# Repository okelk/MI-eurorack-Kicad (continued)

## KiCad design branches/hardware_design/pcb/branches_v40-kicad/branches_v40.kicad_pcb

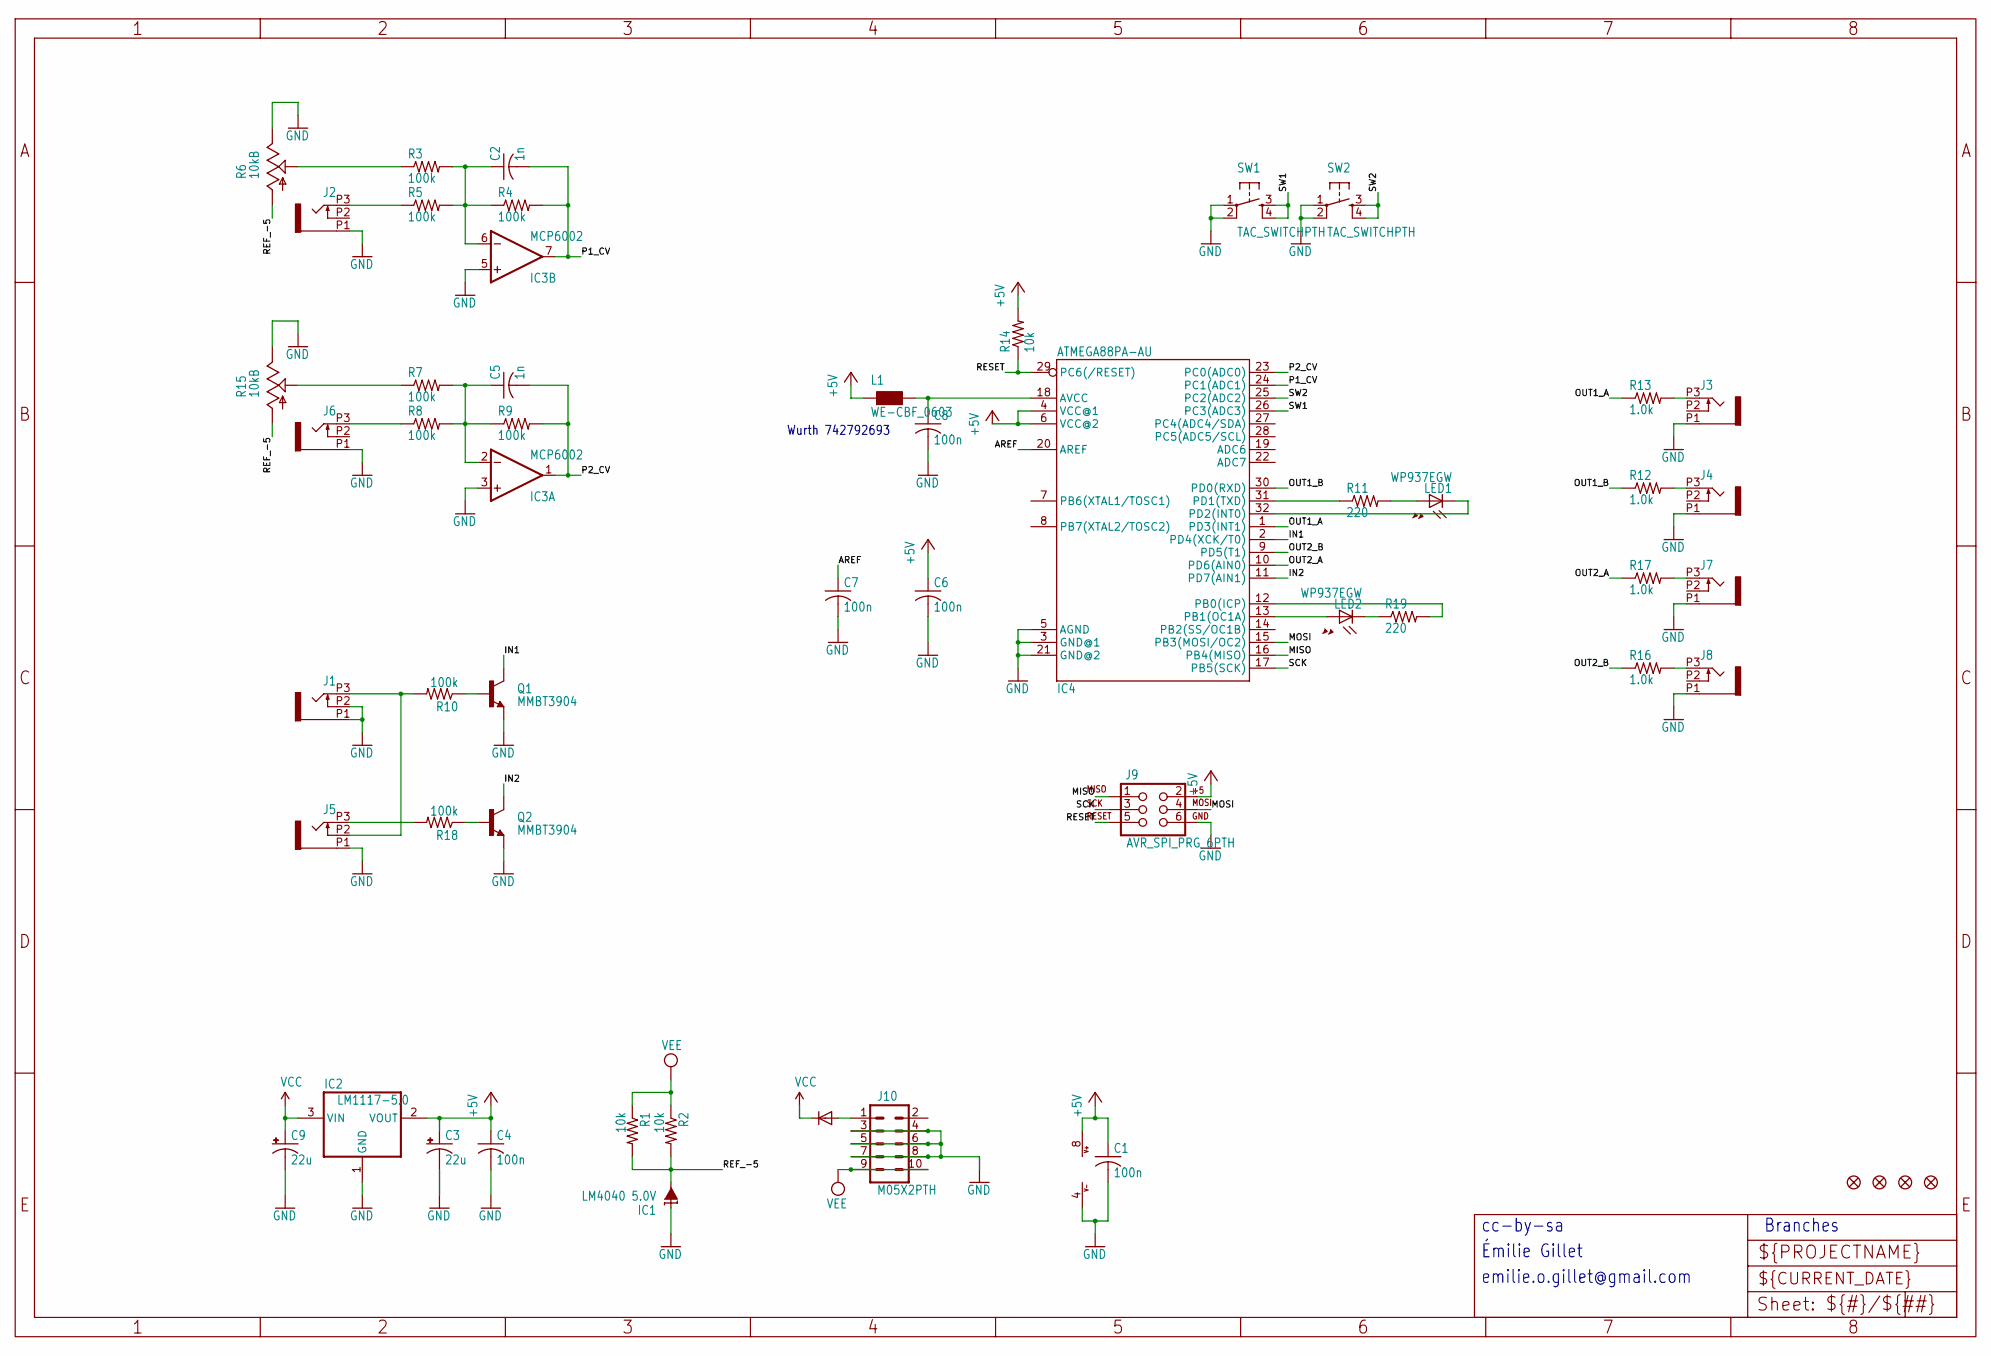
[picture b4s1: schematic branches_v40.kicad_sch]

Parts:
C1, C4, C6, C7, C8: 100n; C0603
C2, C5: 1n; C0603
C3, C9: 22u; PANASONIC_C
D1: 1N5819HW; SOD123
F1, F2, F3, F4: FIDUCIAL1X2; FIDUCIAL-1X2
IC1: LM4040 5.0V; DBZ_R-PDSO-G3
IC2: LM1117-5.0; SOT223
IC3: MCP6002; SO08
IC4: ATMEGA88PA-AU; TQFP32-08
J1, J2, J3, J4, J5, J6, J7, J8: PJ301_THONKICONN6; WQP_PJ_301M6
J9: AVR_SPI_PRG_6PTH; 2X3
J10: M05X2PTH; AVR_ICSP
L1: WE-CBF_0603; 0603
LED1, LED2: WP937EGW; LED3MM
Q1, Q2: MMBT3904; SOT23-BEC
R1, R2, R14: 10k; R0603
R3, R4, R5, R7, R8, R9, R10, R18: 100k; R0603
R6, R15: 10kB; ALPS_POT_VERTICAL_PS
R11, R19: 220; R0603
R12, R13, R16, R17: 1.0k; R0603
SW1, SW2: TAC_SWITCHPTH; TACTILE-PTH

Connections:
+5V: C1.1, C3.+, C4.1, C6.1, IC2.2 (VOUT), IC3.8 (V+), IC4.4 (VCC@1), IC4.6 (VCC@2), J9.2, L1.1, R14.2
AREF: C7.1, IC4.20 (AREF)
GATE1_IN: J1.P3 (3), J5.P2 (2), R10.2
GATE2_IN: J5.P3 (3), R18.2
GND: C1.2, C3.-, C4.2, C6.2, C7.2, C8.2, C9.-, IC1.1 (C), IC2.1 (GND), IC3.3 (+IN), IC3.4 (V-), IC3.5 (+IN), IC4.3 (GND@1), IC4.5 (AGND), IC4.21 (GND@2), J1.P1 (1), J1.P2 (2), J2.P1 (1), J3.P1 (1), J4.P1 (1), J5.P1 (1), J6.P1 (1), J7.P1 (1), J8.P1 (1), J9.6, J10.3, J10.4, J10.5, J10.6, J10.7, J10.8, Q1.E, Q2.E, R6.P$1 (E), R15.P$1 (E), SW1.1, SW1.2, SW2.1, SW2.2
IN1: IC4.2 (PD4(XCK/T0)), Q1.C
IN2: IC4.11 (PD7(AIN1)), Q2.C
MISO: IC4.16 (PB4(MISO)), J9.1
MOSI: IC4.15 (PB3(MOSI/OC2)), J9.4
unnamed: Q1.B, R10.1
unnamed: Q2.B, R18.1
unnamed: D1.A, J10.1
unnamed: C5.1, IC3.2 (-IN), R7.2, R8.2, R9.1
unnamed: J8.P3 (3), R16.2
unnamed: R7.1, R15.P$2 (S)
unnamed: R3.1, R6.P$2 (S)
unnamed: J2.P3 (3), R5.1
unnamed: J6.P3 (3), R8.1
unnamed: IC4.31 (PD1(TXD)), R11.1
unnamed: LED1.A, R11.2
unnamed: IC4.32 (PD2(INT0)), LED1.K (C)
unnamed: IC4.13 (PB1(OC1A)), LED2.A
unnamed: LED2.K (C), R19.1
unnamed: IC4.12 (PB0(ICP)), R19.2
unnamed: C2.1, IC3.6 (-IN), R3.2, R4.1, R5.2
unnamed: J3.P3 (3), R13.2
unnamed: J4.P3 (3), R12.2
unnamed: J7.P3 (3), R17.2
unnamed: C8.1, IC4.18 (AVCC), L1.2
OUT1_A: IC4.1 (PD3(INT1)), R13.1
OUT1_B: IC4.30 (PD0(RXD)), R12.1
OUT2_A: IC4.10 (PD6(AIN0)), R17.1
OUT2_B: IC4.9 (PD5(T1)), R16.1
P1_CV: C2.2, IC3.7 (OUT), IC4.24 (PC1(ADC1)), R4.2
P2_CV: C5.2, IC3.1 (OUT), IC4.23 (PC0(ADC0)), R9.2
REF_-5: IC1.2 (A), R1.2, R2.2, R6.P$3 (A), R15.P$3 (A)
RESET: IC4.29 (PC6(/RESET)), J9.5, R14.1
SCK: IC4.17 (PB5(SCK)), J9.3
SW1: IC4.26 (PC3(ADC3)), SW1.3, SW1.4
SW2: IC4.25 (PC2(ADC2)), SW2.3, SW2.4
VCC: C9.+, D1.C, IC2.3 (VIN)
VEE: J10.9, J10.10, R1.1, R2.1

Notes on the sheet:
cc-by-sa
Branches
emilie.o.gillet@gmail.com
Wurth 742792693
Émilie Gillet

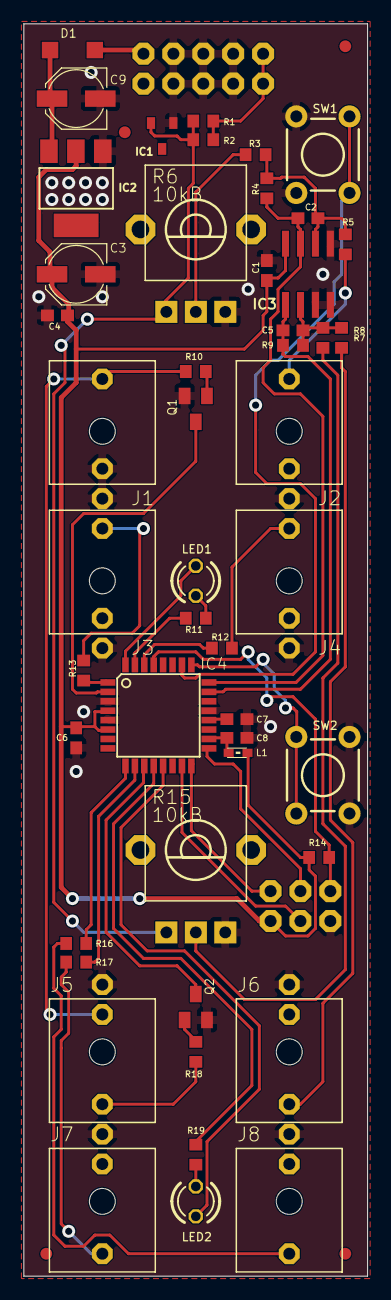
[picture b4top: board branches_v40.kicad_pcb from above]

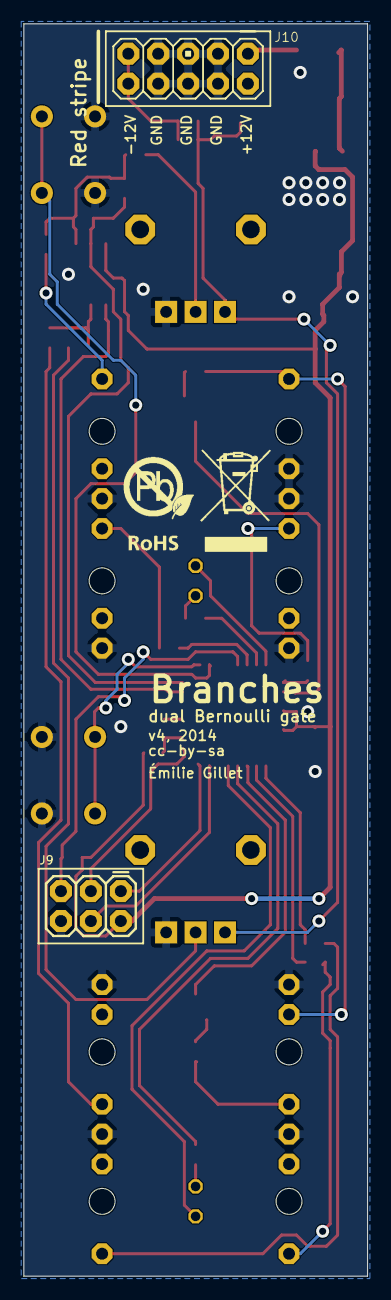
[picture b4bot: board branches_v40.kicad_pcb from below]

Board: 2 copper layers, 29.2 x 106.4 mm, 55 parts (3 on the bottom side), 42 nets.

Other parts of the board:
U$1: ROHS

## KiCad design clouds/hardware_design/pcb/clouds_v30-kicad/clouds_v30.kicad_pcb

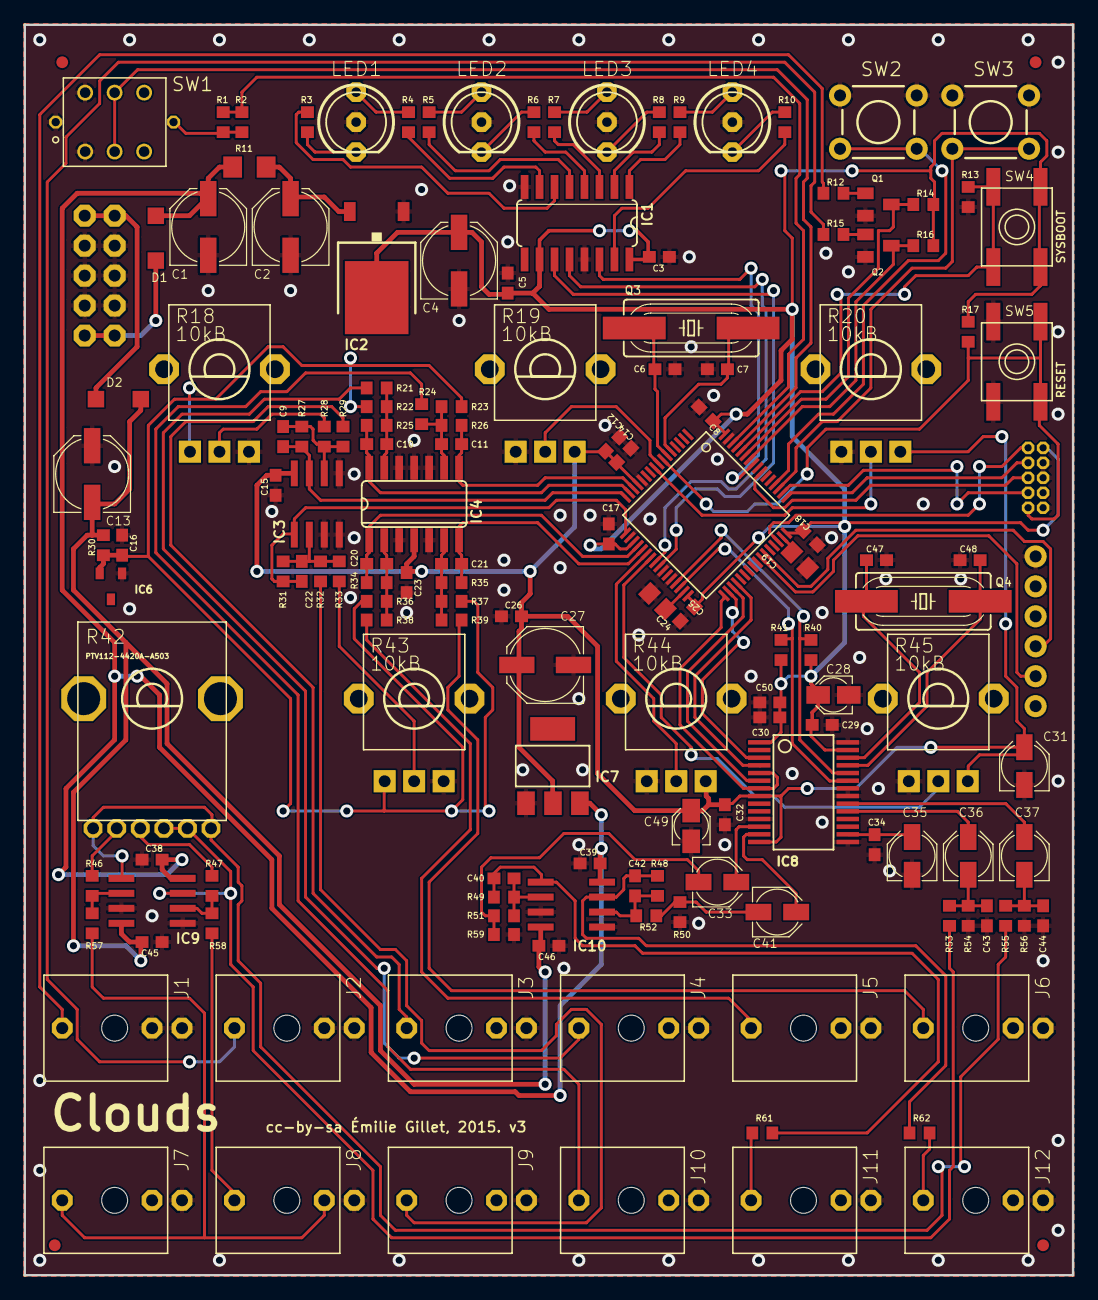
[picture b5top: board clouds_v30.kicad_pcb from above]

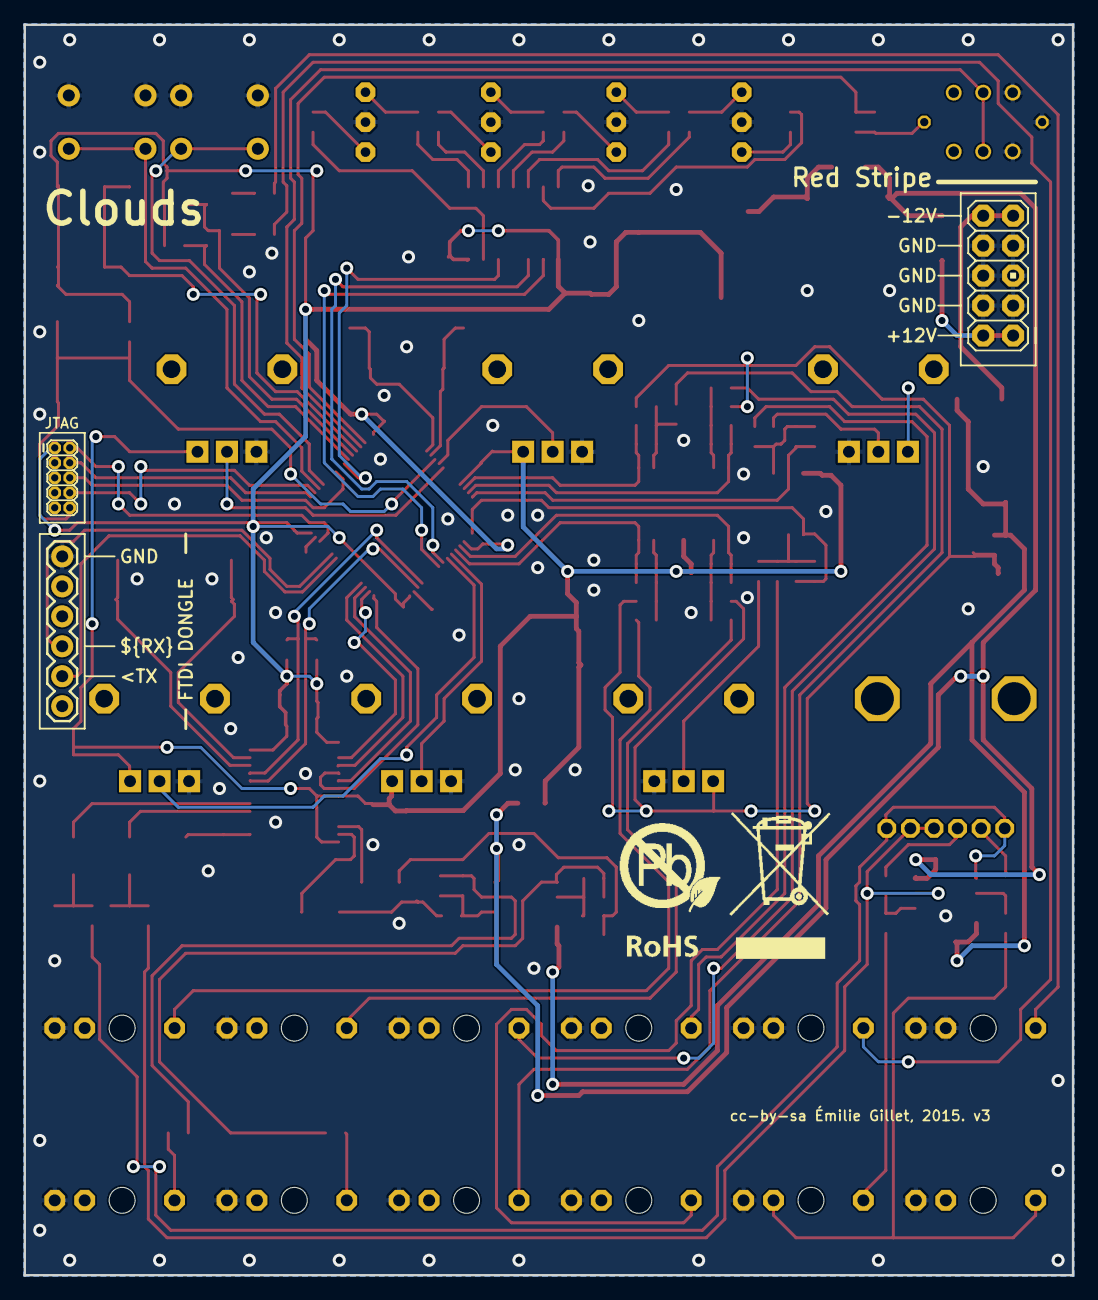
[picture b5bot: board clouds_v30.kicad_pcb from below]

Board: 2 copper layers, 88.9 x 106.0 mm, 156 parts (4 on the bottom side), 106 nets.

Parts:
C1, C2, C4, C13, C27: 47u; PANASONIC_D
C3, C5, C8, C14, C15, C16, C17, C18, C23, C25, C26, C29, C30, C32, C34, C38, C39, C45, C46: 100n; C0603
C6, C7, C40, C42, C47, C48: 18p; C0603
C9, C10, C11, C20, C21, C22: 1n; C0603
C12, C50: 1u; C0603
C19, C24: 2.2u; C0805
C28, C49: 10u; PANASONIC_A
C31, C33, C35, C36, C37, C41: 10u; PANASONIC_B
C43, C44: 220p; C0603
D1, D2: 1N5819HW; SOD123
F1, F2, F3, F4: FIDUCIAL1X2; FIDUCIAL-1X2
IC1: 74HC595D; SO16
IC2: LM1117-3.3; TO252
IC3: MCP6002; SO08
IC4: MCP6004; SO14
IC5: STM32F405RGT6; TQFP-10X10-64
IC6: LM4040B10; DBZ_R-PDSO-G3
IC7: LM1117-3.3; SOT223
IC8: WM8731; SSOP28
IC9, IC10: TL072D; SO08
J1, J2, J3, J4, J5, J6, J7, J8, J9, J10, J11, J12: PJ301_THONKICONN6; WQP_PJ_301M6
JP1: 1X06
JP2: M05X2MINIJTAG; 2X5-1.27
JP3: M05X2PTH; AVR_ICSP
LED1, LED2, LED3, LED4: WP59EGW; LED-BICOLOR-THROUGHHOLE-5MM
Q1, Q2: MMBT3904; SOT23-BEC
Q3: 8MHz; HC49UP
Q4: 12.288MHz; HC49UP
R1, R2, R3, R4, R5, R6, R7, R8, R9, R10: 68; R0603
R11: 4.7; R1206
R12, R15, R21, R24, R29, R32, R38, R39: 100k; R0603
R13, R14, R16, R17: 10k; R0603
R18, R19, R20, R43, R44, R45: 10kB; ALPS_POT_VERTICAL_PS
R22, R23, R28, R33, R37: 200k; R0603
R25, R26, R35: 33k; R0603
R27, R31: 66.5k; R0603
R30: 470; R0603
R34: 47k; R0603
R36: 180k; R0603
R40, R41: 2.2k; R0603
R42: PTV112-4420A-A503; BOURNS_PTV112
R46, R47: 3.3k; R0603
R48, R49, R50, R59: 39k; R0603
R51, R52, R53, R54, R55, R56: 5.6k; R0603
R57, R58: 22k; R0603
R61, R62: 1.0k; R0603
SW1: LP4OA1PBCT
SW2, SW3: TACTILE-PTH
SW4, SW5: EVQ-Q2
U$2: ROHS_BIG

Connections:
+3V3: C3.1, C4.+, C5.1, C8.1, C17.1, C18.1, C25.1, C28.+, C29.1, C30.1, C50.1, IC1.10, IC1.16, IC2.3, IC5.19, IC5.32, IC5.48, IC5.64, IC8.1, IC8.27, JP2.1, R14.2, R16.2, R17.2, R40.2, R41.2, SW4.B, SW4.B'
+3V3_A: C12.1, C14.1, C15.1, C23.1, C26.1, C27.+, C31.+, C32.1, C49.+, IC3.8, IC4.4, IC5.13, IC7.2, IC8.8, IC8.14, R19.P$1, R20.P$1, R44.P$1, R45.P$1
AREF_-10: C16.1, IC6.2, R18.P$3, R22.2, R23.2, R30.2, R36.2, R37.2, R43.P$3
BLEND_CV: C21.2, IC4.7, IC5.21, R35.1
BLEND_POT: IC5.23, R45.P$2
BOOT_FLASH: IC5.60, R13.2, SW4.A, SW4.A'
DENSITY_CV: C22.2, IC3.1, IC5.17, R31.1
GND: C1.-, C2.-, C3.2, C4.-, C5.2, C6.1, C7.1, C8.2, C12.2, C13.+, C14.2, C15.2, C16.2, C17.2, C18.2, C19.2, C23.2, C24.2, C25.2, C26.2, C27.-, C28.-, C29.2, C30.2, C31.-, C32.2, C34.2, C35.-, C38.2, C39.2, C43.2, C44.2, C45.1, C46.1, C47.1, C48.1, C49.-, C50.2, IC1.8, IC1.13, IC2.1, IC3.3, IC3.4, IC3.5, IC4.3, IC4.5, IC4.10, IC4.11, IC4.12, IC5.12, IC5.18, IC5.26, IC5.28, IC5.63, IC6.1, IC7.1, IC8.11, IC8.15, IC8.21, IC8.22, IC8.28, IC9.3, IC9.5, IC10.3, IC10.5, J1.P1, J1.P2, J2.P1, J2.P2, J3.P1, J4.P1, J5.P1, J6.P1, J7.P1, J8.P1, J9.P1, J10.P1, J11.P1, J12.P1, JP1.1, JP2.3, JP2.5, JP2.9, JP3.3, JP3.4, JP3.5, JP3.6, JP3.7, JP3.8, LED1.2, LED2.2, LED3.2, LED4.2, Q1.E, Q2.E, R13.1, R18.P$1, R19.P$3, R20.P$3, R43.P$1, R44.P$3, R45.P$3, R50.1, R54.1, R56.1, R59.1, SW1.L2, SW1.P3, SW1.P6, SW2.1, SW2.2, SW3.1, SW3.2, SW5.A, SW5.A'
I2C_SCL: IC5.29, IC8.24, R40.1
I2C_SDA: IC5.30, IC8.23, R41.1
I2S_LRCK: IC5.33, IC8.5, IC8.7
I2S_SCK: IC5.34, IC8.3
I2S_SIN: IC5.35, IC8.6
I2S_SOUT: IC5.36, IC8.4
JTCK: IC5.49, JP2.4
JTDI: IC5.50, JP2.8
JTDO: IC5.55, JP2.6
JTMS: IC5.46, JP2.2
LED_DATA: IC1.14, IC5.57
LED_EN: IC1.12, IC5.24
LED_REC: IC5.62, R1.1, R2.1
LED_SCK: IC1.11, IC5.25
LIN: C37.+, IC8.20
LOUT: C33.+, IC8.12
LOUT_JACK: J11.P3, R61.1
unnamed: J4.P3, R21.2
unnamed: C10.1, IC4.13, R21.1, R22.1, R25.2
unnamed: J10.P3, R24.2
unnamed: C11.1, IC4.9, R23.1, R24.1, R26.2
unnamed: J6.P3, R39.2
unnamed: C7.2, IC5.5, Q3.2
unnamed: C6.2, IC5.6, Q3.1
unnamed: LED4.3, R9.1
unnamed: J5.P3, R38.2
unnamed: C20.1, IC4.2, R34.2, R36.1, R38.1
unnamed: LED4.1, R10.1
unnamed: C19.1, IC5.47
unnamed: J9.P3, R32.2
unnamed: C21.1, IC4.6, R35.2, R37.1, R39.1
unnamed: LED3.1, R8.1
unnamed: C34.1, C35.+, IC8.16
unnamed: C37.-, C44.1, R55.1, R56.2
unnamed: C24.1, IC5.31
unnamed: J8.P3, R58.2
unnamed: J7.P3, J8.P2, R57.2
unnamed: C36.-, C43.1, R53.1, R54.2
unnamed: C41.-, R50.2, R52.2
unnamed: C22.1, IC3.2, R31.2, R32.1, R33.1
unnamed: C42.1, IC10.6, R48.2, R52.1
unnamed: R33.2, R43.P$2
unnamed: J3.P3, R29.2
unnamed: C42.2, IC10.7, R48.1, R62.2
unnamed: LED3.3, R7.1
unnamed: C9.1, IC3.6, R27.2, R28.1, R29.1
unnamed: C33.-, R51.2, R59.2
unnamed: C40.1, IC10.2, R49.2, R51.1
unnamed: C40.2, IC10.1, R49.1, R61.2
unnamed: LED2.1, R6.1
unnamed: R18.P$2, R28.2
unnamed: J2.P3, R15.1
unnamed: Q2.B, R15.2
unnamed: R1.2, R2.2, SW1.L1
unnamed: LED2.3, R5.1
unnamed: LED1.1, R3.1
unnamed: LED1.3, R4.1
unnamed: IC9.7, R42.2P, R42.3P, R53.2
unnamed: IC1.15, R10.2
unnamed: IC1.1, R9.2
unnamed: IC1.2, R8.2
unnamed: IC1.3, R7.2
unnamed: IC1.4, R6.2
unnamed: IC1.5, R5.2
unnamed: IC1.6, R3.2
unnamed: IC1.7, R4.2
unnamed: IC9.1, R42.2, R42.3, R55.2
unnamed: R42.1P, R47.1
unnamed: R42.1, R46.1
unnamed: IC9.6, R47.2, R58.1
unnamed: C2.+, IC2.2, R11.2
unnamed: D1.A, JP3.1, JP3.2
unnamed: J1.P3, R12.1
unnamed: IC9.2, R46.2, R57.1
unnamed: C47.2, IC8.26, Q4.1
unnamed: C48.2, IC8.25, Q4.2
unnamed: D2.C, JP3.9, JP3.10
unnamed: Q1.B, R12.2
PITCH_POT: IC5.9, R20.P$2
PLAY: IC5.58, Q2.C, R16.1
POSITION_POT_CV: C9.2, IC3.7, IC5.16, R27.1
REC: IC5.59, Q1.C, R14.1
RESET: IC5.7, JP2.10, R17.1, SW5.B, SW5.B'
RIN: C36.+, IC8.19
ROUT: C41.+, IC8.13
ROUT_JACK: J12.P3, R62.1
RX: IC5.43, JP1.4
SIZE_CV: C10.2, IC4.14, IC5.15, R25.1
SIZE_POT: IC5.8, R19.P$2
SW_LOAD: IC5.51, SW3.3, SW3.4
SW_MODE: IC5.52, SW2.3, SW2.4
SW_REC: IC5.61, SW1.P2, SW1.P5
TEXTURE_CV: C11.2, IC4.8, IC5.14, R26.1
TEXTURE_POT: IC5.22, R44.P$2
TX: IC5.42, JP1.5
VCC: C1.+, C38.1, C39.1, D1.C, IC7.3, IC9.8, IC10.8, R11.1
VEE: C13.-, C45.2, C46.2, D2.A, IC9.4, IC10.4, R30.1
V_OCT: C20.2, IC4.1, IC5.20, R34.1

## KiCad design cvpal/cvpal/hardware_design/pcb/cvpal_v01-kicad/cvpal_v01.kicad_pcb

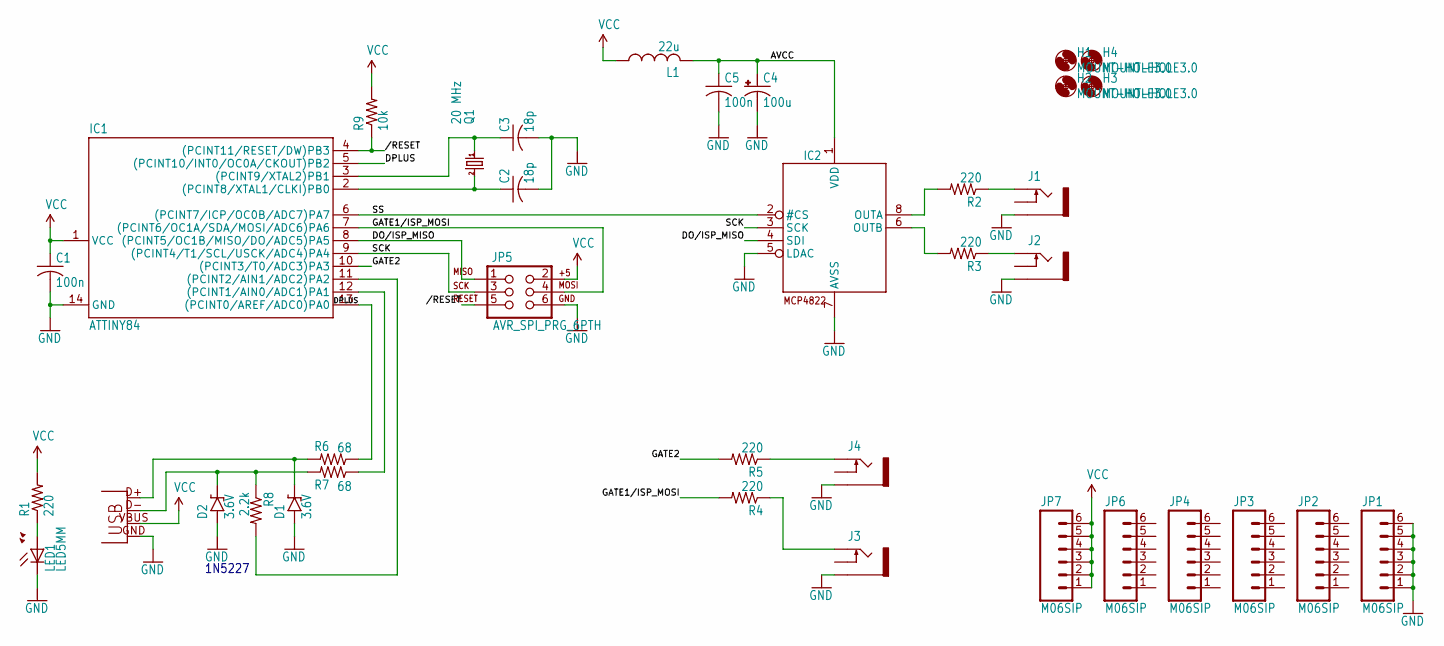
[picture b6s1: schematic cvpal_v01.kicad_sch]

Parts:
C1, C5: 100n; C025-025X050
C2, C3: 18p; C025-025X050
C4: 100u; E2,5-7
D1, D2: 3.6V; D-5
H1, H2, H3, H4: MOUNT-HOLE3.0; 3,0
IC1: ATTINY84; DIL14
IC2: MCP4822; DIL08
J1, J2, J3, J4: 1503_12
JP1, JP2, JP3, JP4, JP6, JP7: M06SIP; 1X06
JP5: AVR_SPI_PRG_6PTH; 2X3
L1: 22u; 0207_10
LED1: LED5MM
Q1: 20 MHz; HC49_S
R1, R2, R3, R4, R5: 220; 0204_7
R6, R7: 68; 0204_7
R8: 2.2k; 0204_7
R9: 10k; 0204_7
X2: USBPTH; USB-B-PTH

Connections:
/RESET: IC1.4 ((PCINT11/RESET/DW)PB3), JP5.5, R9.1
AVCC: C4.+, C5.1, IC2.1 (VDD), L1.2
CV1: IC2.8 (OUTA), R2.2
CV1_R: J1.3 (2), R2.1
CV2: IC2.6 (OUTB), R3.2
D+: D1.C, R6.2, X2.D+
D-: D2.C, R7.2, R8.1, X2.D-
DMINUS: IC1.12 ((PCINT1/AIN0/ADC1)PA1), R7.1
DO/ISP_MISO: IC1.8 ((PCINT5/OC1B/MISO/DO/ADC5)PA5), IC2.4 (SDI), JP5.1
DPLUS: IC1.5 ((PCINT10/INT0/OC0A/CKOUT)PB2), IC1.13 ((PCINT0/AREF/ADC0)PA0), R6.1
GATE1/ISP_MOSI: IC1.7 ((PCINT6/OC1A/SDA/MOSI/ADC6)PA6), JP5.4, R4.2
GATE2: IC1.10 ((PCINT3/T0/ADC3)PA3), R5.2
GND: C1.2, C2.2, C3.2, C4.-, C5.2, D1.A, D2.A, IC1.14 (GND), IC2.5 (LDAC), IC2.7 (AVSS), J1.5 (1), J2.5 (1), J3.5 (1), J4.5 (1), JP1.1, JP1.2, JP1.3, JP1.4, JP1.5, JP1.6, JP5.6, LED1.K (C), X2.GND
unnamed: LED1.A, R1.1
unnamed: C3.1, IC1.3 ((PCINT9/XTAL2)PB1), Q1.1
unnamed: C2.1, IC1.2 ((PCINT8/XTAL1/CLKI)PB0), Q1.2
unnamed: J2.3 (2), R3.1
unnamed: J4.3 (2), R5.1
unnamed: IC1.11 ((PCINT2/AIN1/ADC2)PA2), R8.2
unnamed: J3.3 (2), R4.1
SCK: IC1.9 ((PCINT4/T1/SCL/USCK/ADC4)PA4), IC2.3 (SCK), JP5.3
SS: IC1.6 ((PCINT7/ICP/OC0B/ADC7)PA7), IC2.2 (#CS)
VCC: C1.1, IC1.1 (VCC), JP5.2, JP7.1, JP7.2, JP7.3, JP7.4, JP7.5, JP7.6, L1.1, R1.2, R9.2, X2.VBUS

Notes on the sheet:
1N5227

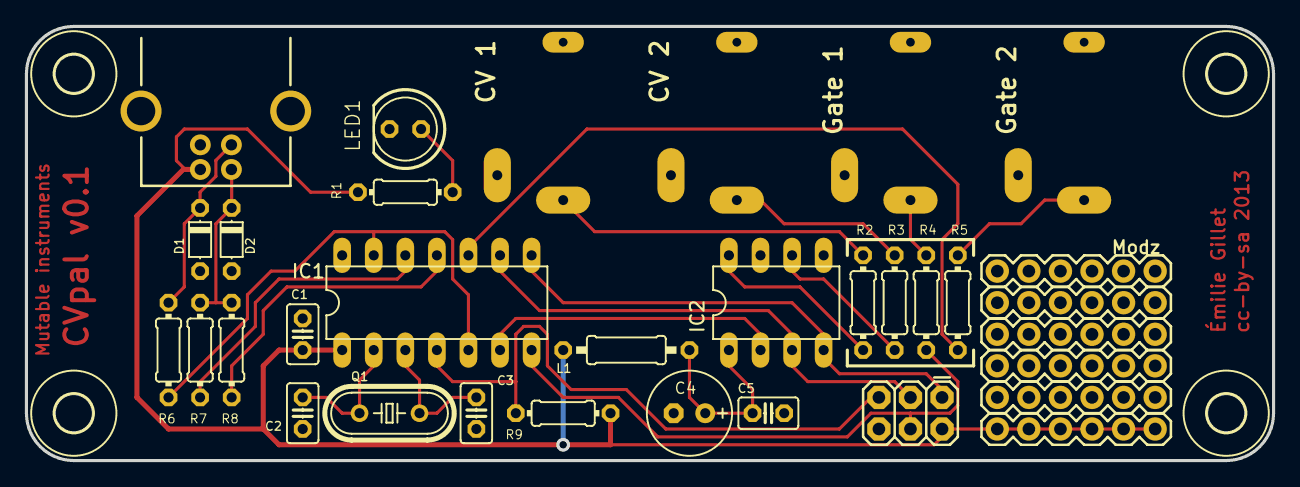
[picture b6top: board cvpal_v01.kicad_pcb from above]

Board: 2 copper layers, 100.3 x 34.9 mm, 37 parts (0 on the bottom side), 23 nets.

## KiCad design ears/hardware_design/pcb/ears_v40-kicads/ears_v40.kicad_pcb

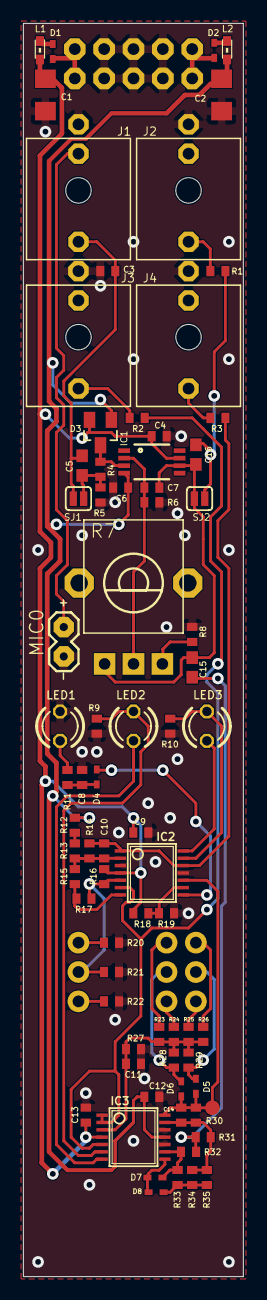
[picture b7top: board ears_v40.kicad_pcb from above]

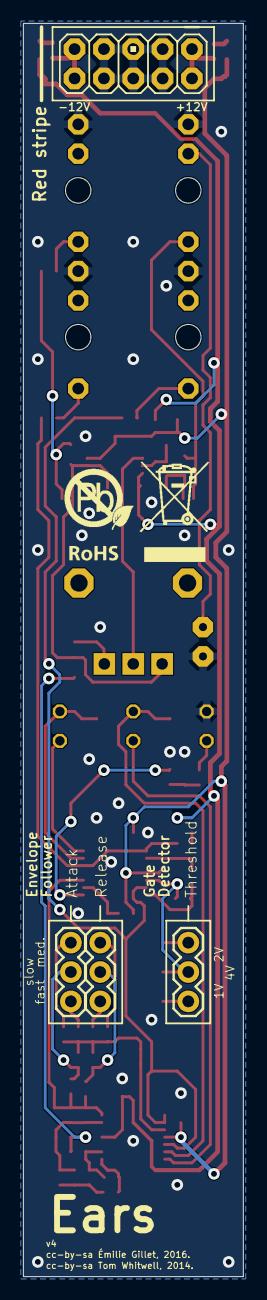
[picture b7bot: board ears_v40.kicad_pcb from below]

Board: 2 copper layers, 19.0 x 108.4 mm, 80 parts (5 on the bottom side), 47 nets.

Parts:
C1, C2: 22u; C1206
C3, C10: 68p; C0402
C4, C6, C9, C12, C13: 100n; C0402
C5, C15, C16: 4.7u; C0603
C7: 22p; C0402
C8, C11: 1u; C0402
C14: 1.0n; C0402
D1, D2: PMEG2010AEB; SOD523
D3: DNP; SOT23
D4, D5, D6, D7, D8: 1N4148; SOD523
IC1: OPA1641; MSOP8
IC2, IC3: LM324PW; TSSOP14
J1, J2, J3, J4: PJ301_THONKICONN6; WQP_PJ_301M6
JP1, JP2, JP3: 1X03
JP4: M05X2PTH; AVR_ICSP
L1, L2: 0603
LED1: WP710A10SEC/J3; LED3MM
LED2: AOL-3MWY4; LED3MM
LED3: WP710A10SEC/J4; LED3MM
MIC0: 1X02_TINY
R1, R2, R3, R8: 510; R0402
R4, R6, R10, R11, R24: 10k; R0402
R5, R27: 1.0M; R0402
R7: 50kB; ALPS_POT_VERTICAL_PS
R9, R18, R22, R26: 20k; R0402
R12, R19, R20, R21, R23, R29, R33, R34, R35: 100k; R0402
R13, R14, R15, R16, R17, R30, R31, R32: 200k; R0402
R25: 2.7k; R0402
R28: 430k; R0402
SJ1, SJ2: SOLDERJUMPERNC; SJ_2S
TP1: TEST-POINT3X5; PAD.03X.05
U$2: ROHS

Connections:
AMP_OUT: C7.2, C15.1, C16.1, IC1.6, R7.P$3, SJ2.1
AMP_OUT_AC: C15.2, R31.1, R32.1
CLIP: D4.A, IC2.8
ENVELOPE: IC2.6, IC3.1, IC3.2, IC3.5, R2.1
FULL_WAVE_RECT: C14.2, D5.A, D6.C, IC2.10, IC3.14, R30.2, TP1.P$1
GATE: C10.2, IC2.1, IC2.12, R3.1, R14.2
GND: C1.2, C2.1, C3.2, C4.2, C6.1, C8.2, C9.2, C11.2, C12.1, C13.2, IC2.3, IC2.11, IC3.10, IC3.12, J1.P1, J2.P1, J3.P1, J4.P1, JP4.3, JP4.4, JP4.5, JP4.6, JP4.7, JP4.8, LED1.K, MIC0.1, R5.1, R6.2, R8.2, R9.2, R10.1, R19.1, R20.2, R21.2, R22.2, R27.1
unnamed: D3.3, IC1.3, R4.1
unnamed: J2.P3, R1.2
unnamed: C3.1, C5.1, J1.P3, SJ1.1
unnamed: D7.A, D8.C, IC3.8
unnamed: D1.A, JP4.1, JP4.2
unnamed: J1.P2, MIC0.2
unnamed: C10.1, IC2.2, R13.2, R14.1, R15.2
unnamed: C7.1, IC1.2, R6.1, R7.P$2
unnamed: C5.2, R4.2, R5.2, SJ1.2
unnamed: D7.C, IC3.9, R32.2, R33.1
unnamed: D8.A, R33.2, R34.1, R35.1
unnamed: R7.P$1, R8.1
unnamed: C14.1, IC3.13, R30.1, R31.2, R34.2, R35.2
unnamed: C16.2, R1.1, SJ2.2
unnamed: J3.P3, R2.2
unnamed: IC3.6, LED2.K, R9.1
unnamed: D5.C, JP1.2, R29.1
unnamed: C11.1, IC3.3, R23.2, R24.2, R25.2, R26.2, R27.2, R28.2, R29.2
unnamed: D2.C, JP4.9, JP4.10
unnamed: JP3.3, R24.1
unnamed: D1.C, L1.2
unnamed: JP3.1, R23.1
unnamed: D6.A, JP3.2, R28.1
unnamed: JP1.1, R25.1
unnamed: JP1.3, R26.1
unnamed: IC2.9, R18.1, R19.2
unnamed: C8.1, D4.C, R11.2
unnamed: IC3.7, LED2.A
unnamed: LED1.A, R11.1
unnamed: J4.P3, R3.2
unnamed: IC2.5, JP2.2, R16.2, R17.1, R21.1
unnamed: JP2.1, R22.1
unnamed: JP2.3, R20.1
unnamed: IC2.13, LED3.K, R10.2
unnamed: IC2.14, LED3.A
unnamed: R12.1, R13.1
unnamed: D2.A, L2.2
VCC: C1.1, C4.1, C9.1, C13.1, D3.2, IC1.7, IC2.4, IC3.4, L1.1, R16.1, R18.2
VEE: C2.2, C6.2, C12.2, D3.1, IC1.4, IC3.11, L2.1, R12.2
~GATE: IC2.7, R15.1, R17.2
